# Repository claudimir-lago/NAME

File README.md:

# NAME — Nanoampere Meter for Electrophoresis

**NAME** is an open-source hardware project for measuring electrophoretic current in capillary electrophoresis (CE) systems. It is intended especially for CE instruments that do not include their own current-measurement system.

NAME is an independent project designed to complement **[Zones](https://github.com/claudimir-lago/Zones)**. NAME provides the electrophoretic current signal, while software such as Zones can use the recorded current for further data treatment, including charge-domain analysis.

> **Project status:** advanced working hardware. NAME has been built, tested, and implemented in four capillary electrophoresis instruments. Release **v1.0.0** provides the open hardware design, manufacturing files, firmware examples, bundled ADS1220 SoftSPI library, and initial technical documentation needed to reproduce and integrate NAME.

## Release

Current public release: **NAME v1.0.0** (2026-10-14).

This release includes the KiCad 10.0 source project, fabrication outputs, BOM, the assembled-board photograph, a PDF schematic, Arduino examples, the `ADS1220_WE_SoftSPI` library, and initial technical documentation.

## Project maturity

NAME is already operational hardware, not an early proof-of-concept. It has been implemented in four CE instruments. Version **1.0.0** is the first public release packaging the working design as a reproducible open-hardware project. See [`docs/project-status.md`](docs/project-status.md).

## Repository contents

- `hardware/kicad/` — editable KiCad 10.0 project files.
- `hardware/gerbers/` — KiCad-generated Gerber and drill fabrication outputs.
- `hardware/fabrication/` — bill of materials (BOM) and manufacturing notes.
- `firmware/libraries/ADS1220_WE_SoftSPI/` — bundled software-SPI ADS1220 library used by the reference implementation.
- `firmware/examples/` — minimal Arduino examples for blocking and non-blocking NAME acquisition.
- `docs/` — operating principle, connector pinout, installation, calibration, testing, and integration documentation.
- `examples/` — example electrophoretic-current data (to be added).
- `images/` — photographs, renderings, and diagrams, including the assembled board shown above and a PDF export of the electrical schematic.

## Hardware

The current design is maintained as a native **KiCad 10.0** project. Project-specific ADS1220 symbol and footprint libraries are included in the repository and are referenced relative to the project directory, so the project does not depend on the original developer's local file paths.

See [`hardware/kicad/README.md`](hardware/kicad/README.md) for details.

## NAME and Zones

NAME and Zones are intentionally separate projects. NAME is responsible for acquisition of the electrophoretic current signal, whereas Zones is data-analysis software.

Documentation will progressively describe recommended data formats and practical integration between the two projects. See [`docs/zones-integration.md`](docs/zones-integration.md).

Zones repository: https://github.com/claudimir-lago/Zones

## Documentation and characterization roadmap

The hardware is already in operational use. The following material will be added to improve reproducibility and provide systematic technical characterization:

- principle of operation (initial documentation included);
- measurement range, resolution, noise, offset, and systematic bandwidth characterization;
- calibration and zero/offset procedures (initial documentation included);
- assembly and first-test procedure;
- connector pinout and interfacing (initial documentation included);
- electrical safety considerations for CE systems (see [`docs/safety.md`](docs/safety.md));
- firmware and Arduino acquisition examples (initial examples are now included);
- validation and performance characterization;
- integration with Zones.

## Licenses

This repository uses separate licenses for software and hardware:

- **NAME-specific firmware, software, and code examples:** GNU General Public License v3.0 or later (`GPL-3.0-or-later`). See [`LICENSE`](LICENSE).
- **Hardware design files:** CERN Open Hardware Licence Version 2 — Strongly Reciprocal (`CERN-OHL-S-2.0`). See [`LICENSE-HARDWARE`](LICENSE-HARDWARE).
- **`ADS1220_WE_SoftSPI`:** MIT License, inherited from Wolfgang (Wolle) Ewald's original [`ADS1220_WE`](https://github.com/wollewald/ADS1220_WE) library. See the library-specific `LICENSE`.

Files may contain more specific licensing notices where appropriate.

## Citation

The [`CITATION.cff`](CITATION.cff) file contains the citation metadata for the **v1.0.0** release. GitHub can use this file to provide a ready-to-copy citation for the project.

## Contributing

Suggestions, test results, corrections, and improvements are welcome. See [`CONTRIBUTING.md`](CONTRIBUTING.md).

## Disclaimer

NAME is an open scientific-instrumentation project that has been implemented in working CE systems. Users are responsible for evaluating electrical safety and suitability for their own CE systems, especially where high voltages are present.

## Fabrication package status

The repository contains KiCad-generated Gerber, drill, and BOM files for the current **single-sided PCB design**. Copper routing is on `B.Cu` only; no `F.Cu` fabrication layer is required for this design. The corrected `Edge.Cuts` output contains only the board profile.

## Arduino integration

Two compact Arduino examples are included. The first shows the minimum blocking readout; the second extracts the interrupt-driven ADS1220 acquisition strategy used in the working [minimalistiCE](https://github.com/lab-laia/minimalistiCE) firmware.

Both examples use the bundled `ADS1220_WE_SoftSPI` library, a software-SPI adaptation of Wolfgang Ewald's `ADS1220_WE`. Software SPI allows NAME to be integrated using freely selected GPIO pins instead of requiring the microcontroller's default hardware SPI pins. The conversion used by the deployed minimalistiCE implementation is made explicit as `NAME_NA_PER_MV = 200.0f`. This factor follows directly from the 5 kOhm Thevenin resistance of R2 and R3. The ADS1220 measurement is differential, and RV1 provides a hardware zero adjustment. An additional calibration factor can be applied when higher absolute accuracy is required. See [`docs/principle-of-operation.md`](docs/principle-of-operation.md). The same document also describes the analog low-pass networks and the additional ADS1220 50/60 Hz digital filtering used in the reference firmware.

## Electrical connections

The current hardware exposes three connectors: J1 for the electrophoretic-current input and shield, J2 for 3–5 V power, and J3 for the ADS1220 digital interface (`DRDY`, `MISO`, `MOSI`, `SCLK`, and `CS`; the sixth `CLK` pin is currently unused). J1 is intended for connection to the **low-voltage electrode** of the CE system. See [`docs/interfacing.md`](docs/interfacing.md) for the complete pinout and minimal installation procedure.

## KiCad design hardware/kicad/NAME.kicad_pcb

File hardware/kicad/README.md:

# KiCad project

This directory contains the editable NAME hardware design in **KiCad 10.0** format.

Core project files:

- `NAME.kicad_pro` — KiCad project configuration
- `NAME.kicad_sch` — electrical schematic
- `NAME.kicad_pcb` — PCB layout

Project-specific libraries:

- `ADS1220_Custom.kicad_sym`
- `ADS1220_Custom.pretty/ADS1220_module.kicad_mod`
- `sym-lib-table`
- `fp-lib-table`

The custom libraries use `${KIPRJMOD}` references and therefore travel with the project. Standard 3D models use `${KICAD10_3DMODEL_DIR}` and are expected to be supplied by a normal KiCad 10 installation.

Local KiCad preference, history, backup, lock, and autosave files are intentionally excluded from version control.

## Hardware license

Unless explicitly stated otherwise, the hardware design files in this directory are licensed under CERN-OHL-S-2.0. See the repository root `LICENSE-HARDWARE` file.

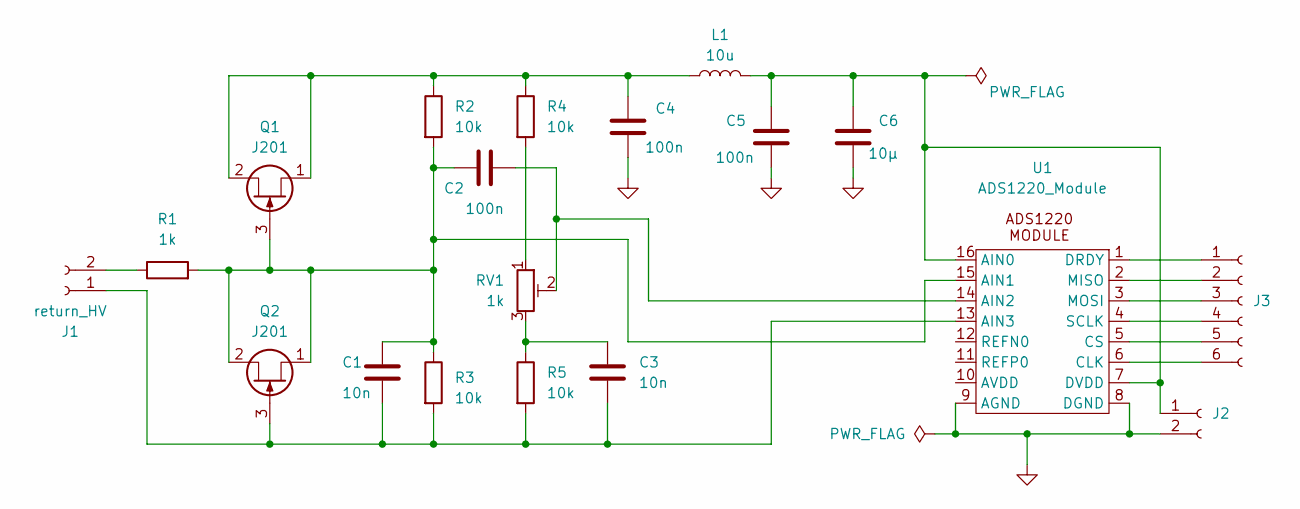
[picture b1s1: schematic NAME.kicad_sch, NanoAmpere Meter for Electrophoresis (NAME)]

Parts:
C1, C3: 10n; C_Disc_D4.7mm_W2.5mm_P5.00mm
C2, C4, C5: 100n; C_Disc_D4.7mm_W2.5mm_P5.00mm
C6: 10µ; CP_Radial_D5.0mm_P2.00mm
J1: return_HV; TerminalBlock_MaiXu_MX126-5.0-02P_1x02_P5.00mm
J2: Conn_01x02_Socket; Molex_KK-254_AE-6410-02A_1x02_P2.54mm_Vertical
J3: Conn_01x06_Socket; Molex_KK-254_AE-6410-06A_1x06_P2.54mm_Vertical
L1: 10u; L_Axial_L5.3mm_D2.2mm_P7.62mm_Horizontal_Vishay_IM-1
Q1, Q2: J201; TO-92L_Inline_Wide
R1: 1k; R_Axial_DIN0207_L6.3mm_D2.5mm_P7.62mm_Horizontal
R2, R3, R4, R5: 10k; R_Axial_DIN0207_L6.3mm_D2.5mm_P7.62mm_Horizontal
RV1: 1k; Potentiometer_Bourns_3296W_Vertical
U1: ADS1220_Module; ADS1220_module

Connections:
GNDA: C4.2, C5.2, C6.2, J2.2, U1.8 (DGND), U1.9 (AGND)
unnamed: C3.1, R5.1, RV1.3
unnamed: C1.2, C3.2, J1.1, Q2.3 (G), R3.2, R5.2, U1.13 (AIN3)
unnamed: J1.2, R1.1
unnamed: C5.1, C6.1, J2.1, L1.2, U1.7 (DVDD), U1.16 (AIN0)
unnamed: J3.1, U1.1 (DRDY)
unnamed: J3.2, U1.2 (MISO)
unnamed: J3.3, U1.3 (MOSI)
unnamed: J3.4, U1.4 (SCLK)
unnamed: J3.5, U1.5 (CS)
unnamed: J3.6, U1.6 (CLK)
unnamed: C4.1, L1.1, Q1.1 (S), Q1.2 (D), R2.1, R4.1
unnamed: C1.1, C2.2, Q1.3 (G), Q2.1 (S), Q2.2 (D), R1.2, R2.2, R3.1, U1.15 (AIN1)
unnamed: R4.2, RV1.1
unnamed: C2.1, RV1.2, U1.14 (AIN2)

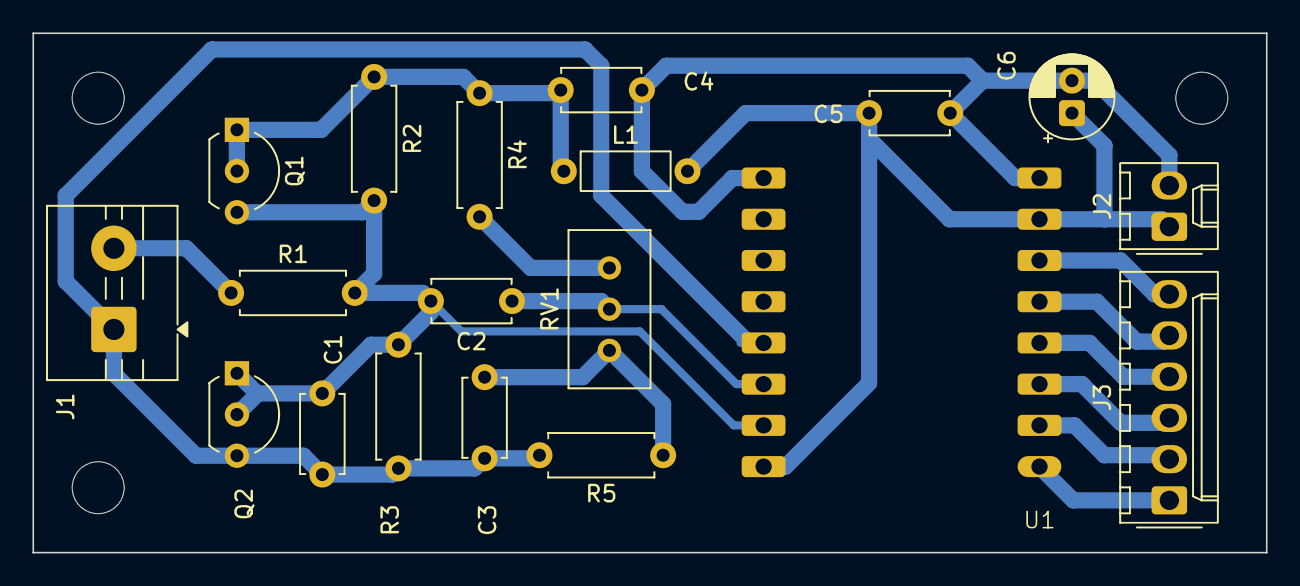
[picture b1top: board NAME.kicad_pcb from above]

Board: 2 copper layers, 76.0 x 32.0 mm, 19 parts (0 on the bottom side), 15 nets.
